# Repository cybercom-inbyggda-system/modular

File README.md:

# modular
Modular extendable signal processing boards

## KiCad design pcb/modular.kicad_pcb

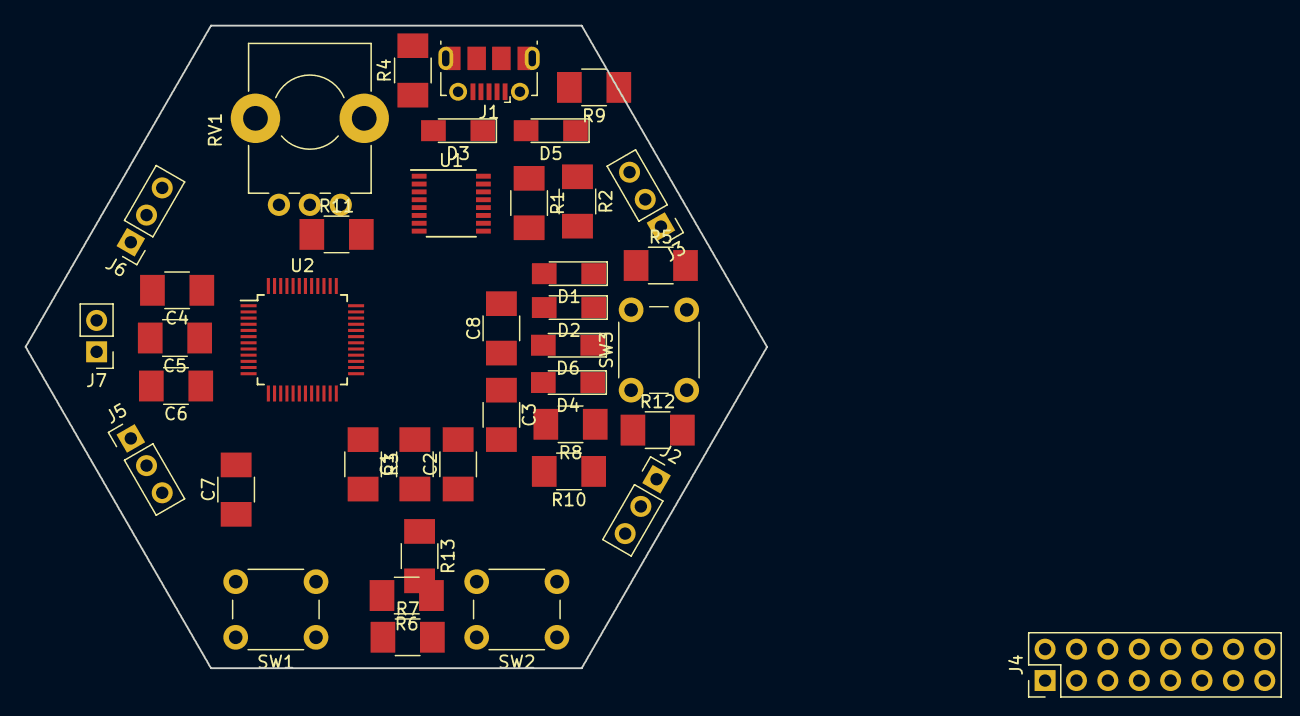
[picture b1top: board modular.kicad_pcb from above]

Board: 2 copper layers, 60.0 x 52.0 mm, 40 parts (0 on the bottom side), 23 nets, no tracks yet.

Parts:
C1, C2: 47p; C_1210_HandSoldering
C3, C4, C5, C7: 100n; C_1210_HandSoldering
C6: 4.7u; C_1210_HandSoldering
C8: C; C_1210_HandSoldering
D1, D2, D4, D6: LED; LED_1206_HandSoldering
D3: RXLED; LED_1206_HandSoldering
D5: TXLED; LED_1206_HandSoldering
J1: USB_OTG; USB_Micro-B_Molex-105017-0001
J2: OUTPUT1; Pin_Header_Straight_1x03_Pitch2.54mm
J3: OUTPUT2; Pin_Header_Straight_1x03_Pitch2.54mm
J4: GPIO; Pin_Header_Straight_2x08_Pitch2.54mm
J5: INPUT1; Pin_Header_Straight_1x03_Pitch2.54mm
J6: INPUT2; Pin_Header_Straight_1x03_Pitch2.54mm
J7: BOOT; Pin_Header_Straight_1x02_Pitch2.54mm
R1: 10k; R_1210_HandSoldering
R2, R6, R7, R13: 4k7; R_1210_HandSoldering
R3, R4: 27; R_1210_HandSoldering
R5, R8, R9, R10, R11, R12: 270; R_1210_HandSoldering
RV1: KNOB; Potentiometer_Alps_RK09K_Horizontal
SW1: BTN1; SW_PUSH_6mm
SW2: BTN2; SW_PUSH_6mm
SW3: RESET; SW_PUSH_6mm
U1: FT230XS-R; SSOP-16_3.9x4.9mm_Pitch0.635mm
U2: STM32F302CCTx; LQFP-48_7x7mm_Pitch0.5mm

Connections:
+3V3: C3.1, D1.2, D2.2, D3.2, D4.2, D5.2, D6.2, J7.2, R6.1, R7.1, RV1.1, U1.10, U1.11, U2.9, U2.24, U2.36, U2.48
/BTN1: R6.2, SW1.1
/BTN2: R7.2, SW2.1
/USART1_RX: U1.1, U2.31
/USART1_TX: U1.4, U2.30
/VBUS_SENSE: R1.1, R2.2, U1.16
GND: C1.2, C2.2, C3.2, C4.2, C5.2, C6.2, C7.1, J1.5, J2.3, J3.3, J5.3, J6.3, R1.2, R13.2, RV1.3, SW1.2, SW2.2, SW3.1, U1.5, U1.6, U1.13, U2.8, U2.23, U2.35, U2.47
unnamed: C1.1, C2.1, J1.3, R3.2
unnamed: C7.2, SW3.2, U2.7
unnamed: D1.1, R5.1
unnamed: D2.1, R8.1
unnamed: D3.1, R9.2
unnamed: D4.1, R10.1
unnamed: D5.1, R11.2
unnamed: D6.1, R12.1
unnamed: J1.1, R2.1
unnamed: J1.2, R4.2
unnamed: J7.1, R13.1, U2.44
unnamed: R3.1, U1.8
unnamed: R4.1, U1.9
unnamed: R9.1, U1.14
unnamed: R11.1, U1.7
VCC: C4.1, C5.1, C6.1, J2.1, J3.1, J5.1, J6.1

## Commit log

2018-04-06 changed folder structure
2018-04-06 Added pcb layout
2018-06-11 Moved all components onto board. First rev.
2018-10-29 Added 1Mbit memory 23lcv1024 to design
2018-11-12 Connect memory to processor
2018-11-26 Connect DACs and ADCs
